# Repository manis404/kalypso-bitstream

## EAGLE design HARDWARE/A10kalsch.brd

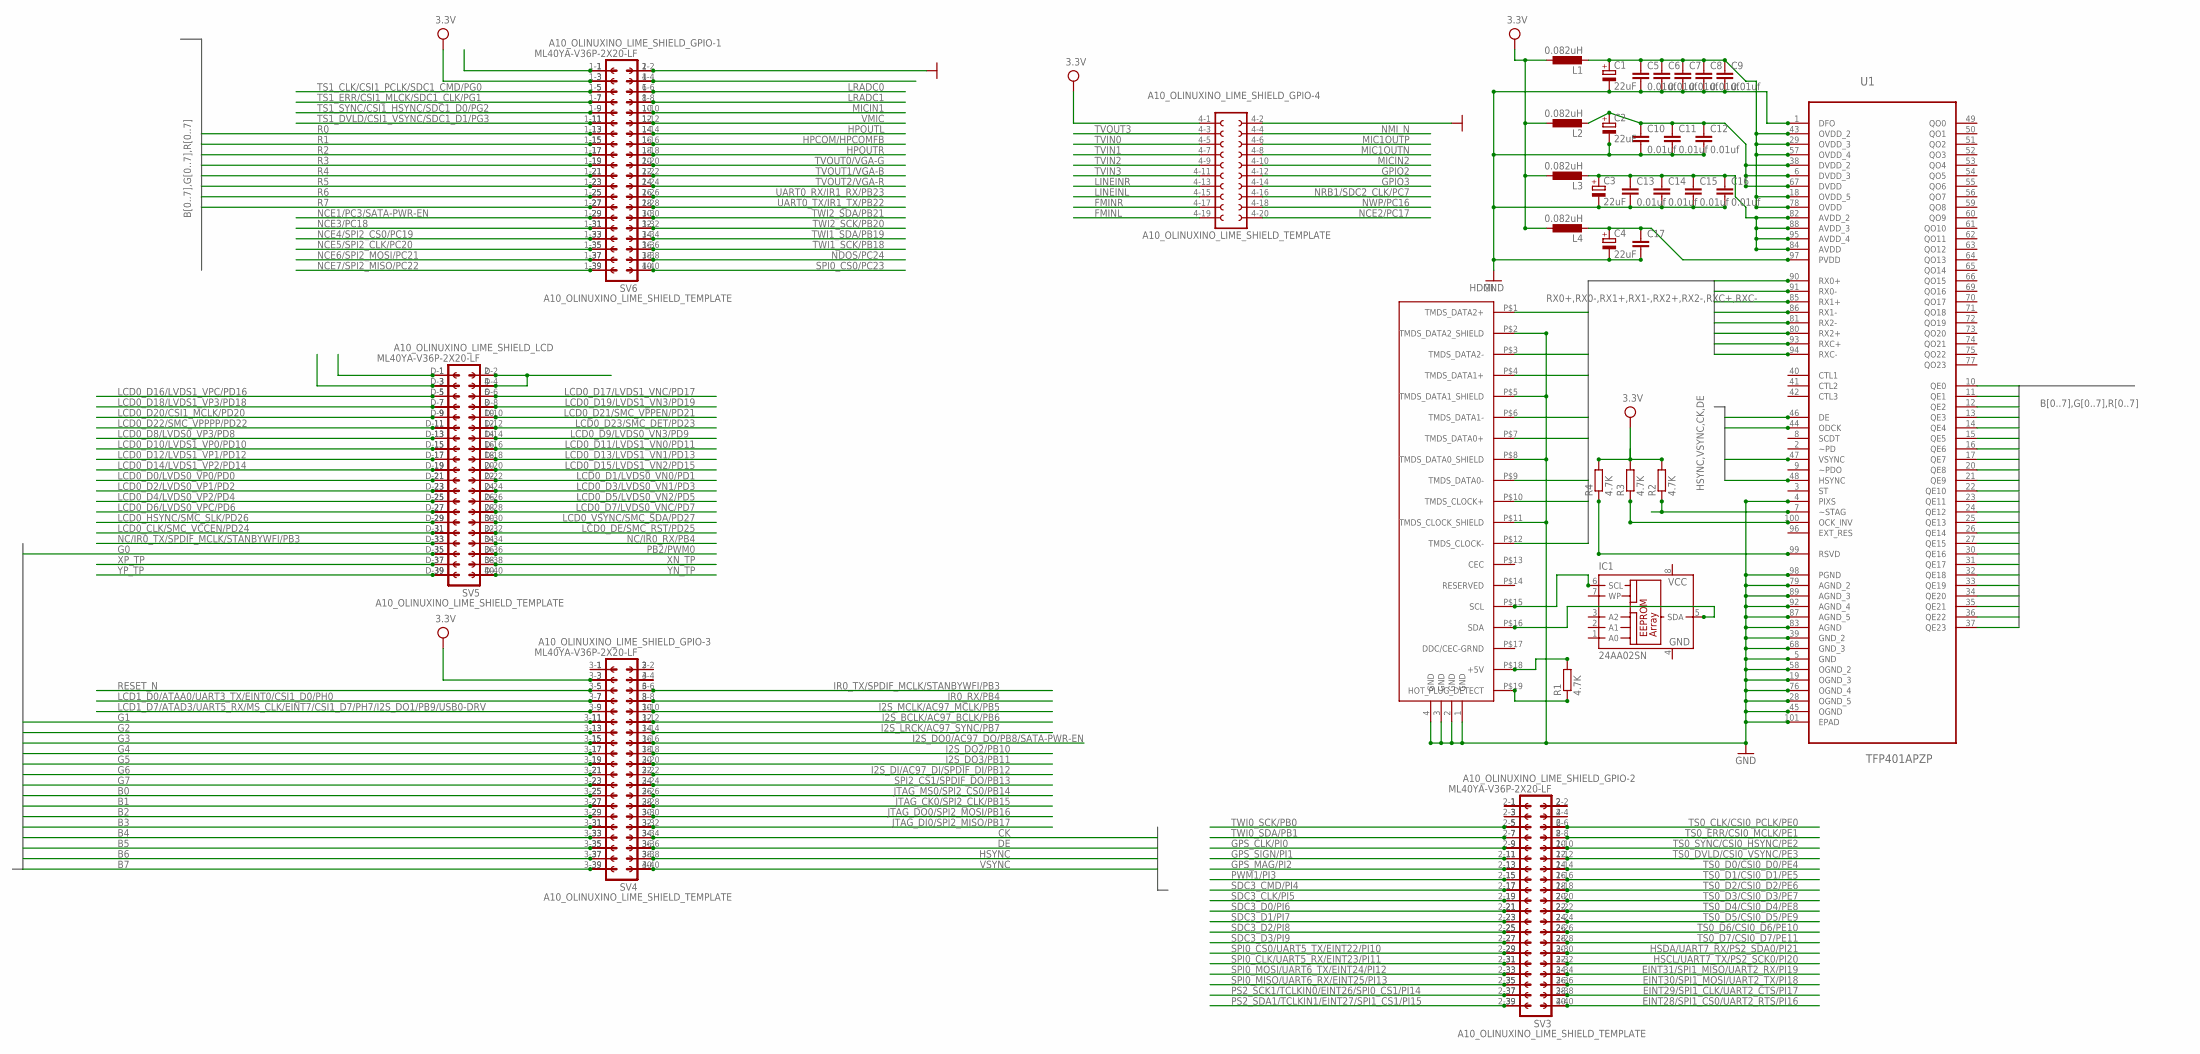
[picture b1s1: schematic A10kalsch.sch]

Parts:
A10_OLINUXINO_LIME_SHIELD: A10_OLINUXINO_LIME_SHIELD_TEMPLATE; A10_OLINUXINO_LIME_SHIELD
C1, C2, C3, C4: 22uF; CT3216
C5, C6, C7, C8, C9, C10, C11, C12, C13, C14, C15, C16: 0.01uf; C0402
C17: C-EUC0402; C0402
HDMI: HDMI; FCI-HDMI
IC1: 24AA02SN; SO-08
L1, L2, L3, L4: 0.082uH; L2012C
R1, R2, R3, R4: 4.7K; R0603
SV3, SV4, SV5, SV6: ML40YA-V36P-2X20-LF; YA-V36P-2X20-LF
U1: TFP401APZP; QFP50P1600X1600X120-101N

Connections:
B0: A10_OLINUXINO_LIME_SHIELD.3-25 (25), SV4.25, U1.10 (QE0)
B1: A10_OLINUXINO_LIME_SHIELD.3-27 (27), SV4.27, U1.11 (QE1)
B2: A10_OLINUXINO_LIME_SHIELD.3-29 (29), SV4.29, U1.12 (QE2)
B3: A10_OLINUXINO_LIME_SHIELD.3-31 (31), SV4.31, U1.13 (QE3)
B4: A10_OLINUXINO_LIME_SHIELD.3-33 (33), SV4.33, U1.14 (QE4)
B5: A10_OLINUXINO_LIME_SHIELD.3-35 (35), SV4.35, U1.15 (QE5)
B6: A10_OLINUXINO_LIME_SHIELD.3-37 (37), SV4.37, U1.16 (QE6)
B7: A10_OLINUXINO_LIME_SHIELD.3-39 (39), SV4.39, U1.17 (QE7)
CK: A10_OLINUXINO_LIME_SHIELD.3-34 (34), SV4.34, U1.44 (ODCK)
DE: A10_OLINUXINO_LIME_SHIELD.3-36 (36), SV4.36, U1.46 (DE)
EINT28/SPI1_CS0/UART2_RTS/PI16: A10_OLINUXINO_LIME_SHIELD.2-40 (40), SV3.40
EINT29/SPI1_CLK/UART2_CTS/PI17: A10_OLINUXINO_LIME_SHIELD.2-38 (38), SV3.38
EINT30/SPI1_MOSI/UART2_TX/PI18: A10_OLINUXINO_LIME_SHIELD.2-36 (36), SV3.36
EINT31/SPI1_MISO/UART2_RX/PI19: A10_OLINUXINO_LIME_SHIELD.2-34 (34), SV3.34
FMINL: A10_OLINUXINO_LIME_SHIELD.4-19 (19)
FMINR: A10_OLINUXINO_LIME_SHIELD.4-17 (17)
G0: A10_OLINUXINO_LIME_SHIELD.D-35 (35), SV5.35, U1.20 (QE8)
G1: A10_OLINUXINO_LIME_SHIELD.3-11 (11), SV4.11, U1.21 (QE9)
G2: A10_OLINUXINO_LIME_SHIELD.3-13 (13), SV4.13, U1.22 (QE10)
G3: A10_OLINUXINO_LIME_SHIELD.3-15 (15), SV4.15, U1.23 (QE11)
G4: A10_OLINUXINO_LIME_SHIELD.3-17 (17), SV4.17, U1.24 (QE12)
G5: A10_OLINUXINO_LIME_SHIELD.3-19 (19), SV4.19, U1.25 (QE13)
G6: A10_OLINUXINO_LIME_SHIELD.3-21 (21), SV4.21, U1.26 (QE14)
G7: A10_OLINUXINO_LIME_SHIELD.3-23 (23), SV4.23, U1.27 (QE15)
GND: A10_OLINUXINO_LIME_SHIELD.1-2 (2), A10_OLINUXINO_LIME_SHIELD.4-2 (2), C1.-, C2.-, C3.-, C4.-, C5.2, C6.2, C7.2, C8.2, C9.2, C10.2, C11.2, C12.2, C13.2, C14.2, C15.2, C16.2, C17.2, HDMI.1 (GND), HDMI.2 (GND), HDMI.3 (GND), HDMI.4 (GND), HDMI.P$2 (TMDS_DATA2_SHIELD), HDMI.P$5 (TMDS_DATA1_SHIELD), HDMI.P$8 (TMDS_DATA0_SHIELD), HDMI.P$11 (TMDS_CLOCK_SHIELD), IC1.4 (GND), SV6.2, U1.1 (DFO), U1.4 (PIXS), U1.5 (GND), U1.19 (OGND_3), U1.28 (OGND_5), U1.39 (GND_2), U1.45 (OGND), U1.58 (OGND_2), U1.68 (GND_3), U1.76 (OGND_4), U1.79 (AGND_2), U1.83 (AGND), U1.87 (AGND_5), U1.89 (AGND_3), U1.92 (AGND_4), U1.98 (PGND), U1.101 (EPAD)
GPIO2: A10_OLINUXINO_LIME_SHIELD.4-12 (12)
GPIO3: A10_OLINUXINO_LIME_SHIELD.4-14 (14)
GPS_CLK/PI0: A10_OLINUXINO_LIME_SHIELD.2-9 (9), SV3.9
GPS_MAG/PI2: A10_OLINUXINO_LIME_SHIELD.2-13 (13), SV3.13
GPS_SIGN/PI1: A10_OLINUXINO_LIME_SHIELD.2-11 (11), SV3.11
HPCOM/HPCOMFB: A10_OLINUXINO_LIME_SHIELD.1-16 (16), SV6.16
HPOUTL: A10_OLINUXINO_LIME_SHIELD.1-14 (14), SV6.14
HPOUTR: A10_OLINUXINO_LIME_SHIELD.1-18 (18), SV6.18
HSCL/UART7_TX/PS2_SCK0/PI20: A10_OLINUXINO_LIME_SHIELD.2-32 (32), SV3.32
HSDA/UART7_RX/PS2_SDA0/PI21: A10_OLINUXINO_LIME_SHIELD.2-30 (30), SV3.30
HSYNC: A10_OLINUXINO_LIME_SHIELD.3-38 (38), SV4.38, U1.48 (HSYNC)
I2S_BCLK/AC97_BCLK/PB6: A10_OLINUXINO_LIME_SHIELD.3-12 (12), SV4.12
I2S_DI/AC97_DI/SPDIF_DI/PB12: A10_OLINUXINO_LIME_SHIELD.3-22 (22), SV4.22
I2S_DO0/AC97_DO/PB8/SATA-PWR-EN: A10_OLINUXINO_LIME_SHIELD.3-16 (16), SV4.16
I2S_DO2/PB10: A10_OLINUXINO_LIME_SHIELD.3-18 (18), SV4.18
I2S_DO3/PB11: A10_OLINUXINO_LIME_SHIELD.3-20 (20), SV4.20
I2S_LRCK/AC97_SYNC/PB7: A10_OLINUXINO_LIME_SHIELD.3-14 (14), SV4.14
I2S_MCLK/AC97_MCLK/PB5: A10_OLINUXINO_LIME_SHIELD.3-10 (10), SV4.10
IR0_RX/PB4: A10_OLINUXINO_LIME_SHIELD.3-8 (8), SV4.8
IR0_TX/SPDIF_MCLK/STANBYWFI/PB3: A10_OLINUXINO_LIME_SHIELD.3-6 (6), SV4.6
JTAG_CK0/SPI2_CLK/PB15: A10_OLINUXINO_LIME_SHIELD.3-28 (28), SV4.28
JTAG_DI0/SPI2_MISO/PB17: A10_OLINUXINO_LIME_SHIELD.3-32 (32), SV4.32
JTAG_DO0/SPI2_MOSI/PB16: A10_OLINUXINO_LIME_SHIELD.3-30 (30), SV4.30
JTAG_MS0/SPI2_CS0/PB14: A10_OLINUXINO_LIME_SHIELD.3-26 (26), SV4.26
LCD0_CLK/SMC_VCCEN/PD24: A10_OLINUXINO_LIME_SHIELD.D-31 (31), SV5.31
LCD0_D0/LVDS0_VP0/PD0: A10_OLINUXINO_LIME_SHIELD.D-21 (21), SV5.21
LCD0_D1/LVDS0_VN0/PD1: A10_OLINUXINO_LIME_SHIELD.D-22 (22), SV5.22
LCD0_D2/LVDS0_VP1/PD2: A10_OLINUXINO_LIME_SHIELD.D-23 (23), SV5.23
LCD0_D3/LVDS0_VN1/PD3: A10_OLINUXINO_LIME_SHIELD.D-24 (24), SV5.24
LCD0_D4/LVDS0_VP2/PD4: A10_OLINUXINO_LIME_SHIELD.D-25 (25), SV5.25
LCD0_D5/LVDS0_VN2/PD5: A10_OLINUXINO_LIME_SHIELD.D-26 (26), SV5.26
LCD0_D6/LVDS0_VPC/PD6: A10_OLINUXINO_LIME_SHIELD.D-27 (27), SV5.27
LCD0_D7/LVDS0_VNC/PD7: A10_OLINUXINO_LIME_SHIELD.D-28 (28), SV5.28
LCD0_D8/LVDS0_VP3/PD8: A10_OLINUXINO_LIME_SHIELD.D-13 (13), SV5.13
LCD0_D9/LVDS0_VN3/PD9: A10_OLINUXINO_LIME_SHIELD.D-14 (14), SV5.14
LCD0_D10/LVDS1_VP0/PD10: A10_OLINUXINO_LIME_SHIELD.D-15 (15), SV5.15
LCD0_D11/LVDS1_VN0/PD11: A10_OLINUXINO_LIME_SHIELD.D-16 (16), SV5.16
LCD0_D12/LVDS1_VP1/PD12: A10_OLINUXINO_LIME_SHIELD.D-17 (17), SV5.17
LCD0_D13/LVDS1_VN1/PD13: A10_OLINUXINO_LIME_SHIELD.D-18 (18), SV5.18
LCD0_D14/LVDS1_VP2/PD14: A10_OLINUXINO_LIME_SHIELD.D-19 (19), SV5.19
LCD0_D15/LVDS1_VN2/PD15: A10_OLINUXINO_LIME_SHIELD.D-20 (20), SV5.20
LCD0_D16/LVDS1_VPC/PD16: A10_OLINUXINO_LIME_SHIELD.D-5 (5), SV5.5
LCD0_D17/LVDS1_VNC/PD17: A10_OLINUXINO_LIME_SHIELD.D-6 (6), SV5.6
LCD0_D18/LVDS1_VP3/PD18: A10_OLINUXINO_LIME_SHIELD.D-7 (7), SV5.7
LCD0_D19/LVDS1_VN3/PD19: A10_OLINUXINO_LIME_SHIELD.D-8 (8), SV5.8
LCD0_D20/CSI1_MCLK/PD20: A10_OLINUXINO_LIME_SHIELD.D-9 (9), SV5.9
LCD0_D21/SMC_VPPEN/PD21: A10_OLINUXINO_LIME_SHIELD.D-10 (10), SV5.10
LCD0_D22/SMC_VPPPP/PD22: A10_OLINUXINO_LIME_SHIELD.D-11 (11), SV5.11
LCD0_D23/SMC_DET/PD23: A10_OLINUXINO_LIME_SHIELD.D-12 (12), SV5.12
LCD0_DE/SMC_RST/PD25: A10_OLINUXINO_LIME_SHIELD.D-32 (32), SV5.32
LCD0_HSYNC/SMC_SLK/PD26: A10_OLINUXINO_LIME_SHIELD.D-29 (29), SV5.29
LCD0_VSYNC/SMC_SDA/PD27: A10_OLINUXINO_LIME_SHIELD.D-30 (30), SV5.30
LCD1_D0/ATAA0/UART3_TX/EINT0/CSI1_D0/PH0: A10_OLINUXINO_LIME_SHIELD.3-7 (7), SV4.7
LCD1_D7/ATAD3/UART5_RX/MS_CLK/EINT7/CSI1_D7/PH7/I2S_DO1/PB9/USB0-DRV: A10_OLINUXINO_LIME_SHIELD.3-9 (9), SV4.9
LINEINL: A10_OLINUXINO_LIME_SHIELD.4-15 (15)
LINEINR: A10_OLINUXINO_LIME_SHIELD.4-13 (13)
LRADC0: A10_OLINUXINO_LIME_SHIELD.1-6 (6), SV6.6
LRADC1: A10_OLINUXINO_LIME_SHIELD.1-8 (8), SV6.8
MIC1OUTN: A10_OLINUXINO_LIME_SHIELD.4-8 (8)
MIC1OUTP: A10_OLINUXINO_LIME_SHIELD.4-6 (6)
MICIN1: A10_OLINUXINO_LIME_SHIELD.1-10 (10), SV6.10
MICIN2: A10_OLINUXINO_LIME_SHIELD.4-10 (10)
unnamed: A10_OLINUXINO_LIME_SHIELD.1-4 (4), SV6.4
unnamed: R2.1, U1.7 (~STAG)
unnamed: R3.1, U1.100 (OCK_INV)
unnamed: R4.1, U1.99 (RSVD)
unnamed: A10_OLINUXINO_LIME_SHIELD.D-3 (3), SV5.3
unnamed: C2.+, C10.1, C11.1, C12.1, L2.2, U1.6 (DVDD_3), U1.38 (DVDD_2), U1.67 (DVDD)
unnamed: C4.+, C17.1, L4.2, U1.97 (PVDD)
unnamed: C3.+, C13.1, C14.1, C15.1, C16.1, L3.2, U1.82 (AVDD_2), U1.84 (AVDD), U1.88 (AVDD_3), U1.95 (AVDD_4)
unnamed: C1.+, C5.1, C6.1, C7.1, C8.1, C9.1, L1.2, U1.18 (OVDD_5), U1.29 (OVDD_3), U1.43 (OVDD_2), U1.57 (OVDD_4), U1.78 (OVDD)
unnamed: A10_OLINUXINO_LIME_SHIELD.D-1 (1), SV5.1
unnamed: A10_OLINUXINO_LIME_SHIELD.D-2 (2), A10_OLINUXINO_LIME_SHIELD.D-4 (4), SV5.2, SV5.4
unnamed: A10_OLINUXINO_LIME_SHIELD.1-1 (1), SV6.1
unnamed: HDMI.P$18 (+5V), R1.2
unnamed: HDMI.P$19 (HOT_PLUG_DETECT), R1.1
unnamed: A10_OLINUXINO_LIME_SHIELD.2-1 (1), SV3.1
unnamed: A10_OLINUXINO_LIME_SHIELD.2-2 (2), SV3.2
unnamed: A10_OLINUXINO_LIME_SHIELD.2-3 (3), SV3.3
unnamed: A10_OLINUXINO_LIME_SHIELD.2-4 (4), SV3.4
unnamed: A10_OLINUXINO_LIME_SHIELD.3-1 (1), SV4.1
unnamed: A10_OLINUXINO_LIME_SHIELD.3-2 (2), SV4.2
unnamed: A10_OLINUXINO_LIME_SHIELD.3-4 (4), SV4.4
unnamed: HDMI.P$15 (SCL), IC1.6 (SCL)
unnamed: HDMI.P$16 (SDA), IC1.5 (SDA)
NC/IR0_RX/PB4: A10_OLINUXINO_LIME_SHIELD.D-34 (34), SV5.34
NC/IR0_TX/SPDIF_MCLK/STANBYWFI/PB3: A10_OLINUXINO_LIME_SHIELD.D-33 (33), SV5.33
NCE1/PC3/SATA-PWR-EN: A10_OLINUXINO_LIME_SHIELD.1-29 (29), SV6.29
NCE2/PC17: A10_OLINUXINO_LIME_SHIELD.4-20 (20)
NCE3/PC18: A10_OLINUXINO_LIME_SHIELD.1-31 (31), SV6.31
NCE4/SPI2_CS0/PC19: A10_OLINUXINO_LIME_SHIELD.1-33 (33), SV6.33
NCE5/SPI2_CLK/PC20: A10_OLINUXINO_LIME_SHIELD.1-35 (35), SV6.35
NCE6/SPI2_MOSI/PC21: A10_OLINUXINO_LIME_SHIELD.1-37 (37), SV6.37
NCE7/SPI2_MISO/PC22: A10_OLINUXINO_LIME_SHIELD.1-39 (39), SV6.39
NDQS/PC24: A10_OLINUXINO_LIME_SHIELD.1-38 (38), SV6.38
NMI_N: A10_OLINUXINO_LIME_SHIELD.4-4 (4)
NRB1/SDC2_CLK/PC7: A10_OLINUXINO_LIME_SHIELD.4-16 (16)
NWP/PC16: A10_OLINUXINO_LIME_SHIELD.4-18 (18)
PB2/PWM0: A10_OLINUXINO_LIME_SHIELD.D-36 (36), SV5.36
PS2_SCK1/TCLKIN0/EINT26/SPI0_CS1/PI14: A10_OLINUXINO_LIME_SHIELD.2-37 (37), SV3.37
PS2_SDA1/TCLKIN1/EINT27/SPI1_CS1/PI15: A10_OLINUXINO_LIME_SHIELD.2-39 (39), SV3.39
PWM1/PI3: A10_OLINUXINO_LIME_SHIELD.2-15 (15), SV3.15
R0: A10_OLINUXINO_LIME_SHIELD.1-13 (13), SV6.13, U1.30 (QE16)
R1: A10_OLINUXINO_LIME_SHIELD.1-15 (15), SV6.15, U1.31 (QE17)
R2: A10_OLINUXINO_LIME_SHIELD.1-17 (17), SV6.17, U1.32 (QE18)
R3: A10_OLINUXINO_LIME_SHIELD.1-19 (19), SV6.19, U1.33 (QE19)
R4: A10_OLINUXINO_LIME_SHIELD.1-21 (21), SV6.21, U1.34 (QE20)
R5: A10_OLINUXINO_LIME_SHIELD.1-23 (23), SV6.23, U1.35 (QE21)
R6: A10_OLINUXINO_LIME_SHIELD.1-25 (25), SV6.25, U1.36 (QE22)
R7: A10_OLINUXINO_LIME_SHIELD.1-27 (27), SV6.27, U1.37 (QE23)
RESET_N: A10_OLINUXINO_LIME_SHIELD.3-5 (5), SV4.5
RX0_N: HDMI.P$9 (TMDS_DATA0-), U1.91 (RX0-)
RX0_P: HDMI.P$7 (TMDS_DATA0+), U1.90 (RX0+)
RX1_N: HDMI.P$6 (TMDS_DATA1-), U1.86 (RX1-)
RX1_P: HDMI.P$4 (TMDS_DATA1+), U1.85 (RX1+)
RX2_N: HDMI.P$3 (TMDS_DATA2-), U1.81 (RX2-)
RX2_P: HDMI.P$1 (TMDS_DATA2+), U1.80 (RX2+)
RXC_N: HDMI.P$12 (TMDS_CLOCK-), U1.94 (RXC-)
RXC_P: HDMI.P$10 (TMDS_CLOCK+), U1.93 (RXC+)
SDC3_CLK/PI5: A10_OLINUXINO_LIME_SHIELD.2-19 (19), SV3.19
SDC3_CMD/PI4: A10_OLINUXINO_LIME_SHIELD.2-17 (17), SV3.17
SDC3_D0/PI6: A10_OLINUXINO_LIME_SHIELD.2-21 (21), SV3.21
SDC3_D1/PI7: A10_OLINUXINO_LIME_SHIELD.2-23 (23), SV3.23
SDC3_D2/PI8: A10_OLINUXINO_LIME_SHIELD.2-25 (25), SV3.25
SDC3_D3/PI9: A10_OLINUXINO_LIME_SHIELD.2-27 (27), SV3.27
SPI0_CLK/UART5_RX/EINT23/PI11: A10_OLINUXINO_LIME_SHIELD.2-31 (31), SV3.31
SPI0_CS0/PC23: A10_OLINUXINO_LIME_SHIELD.1-40 (40), SV6.40
SPI0_CS0/UART5_TX/EINT22/PI10: A10_OLINUXINO_LIME_SHIELD.2-29 (29), SV3.29
SPI0_MISO/UART6_RX/EINT25/PI13: A10_OLINUXINO_LIME_SHIELD.2-35 (35), SV3.35
SPI0_MOSI/UART6_TX/EINT24/PI12: A10_OLINUXINO_LIME_SHIELD.2-33 (33), SV3.33
SPI2_CS1/SPDIF_DO/PB13: A10_OLINUXINO_LIME_SHIELD.3-24 (24), SV4.24
TS0_CLK/CSI0_PCLK/PE0: A10_OLINUXINO_LIME_SHIELD.2-6 (6), SV3.6
TS0_D0/CSI0_D0/PE4: A10_OLINUXINO_LIME_SHIELD.2-14 (14), SV3.14
TS0_D1/CSI0_D1/PE5: A10_OLINUXINO_LIME_SHIELD.2-16 (16), SV3.16
TS0_D2/CSI0_D2/PE6: A10_OLINUXINO_LIME_SHIELD.2-18 (18), SV3.18
TS0_D3/CSI0_D3/PE7: A10_OLINUXINO_LIME_SHIELD.2-20 (20), SV3.20
TS0_D4/CSI0_D4/PE8: A10_OLINUXINO_LIME_SHIELD.2-22 (22), SV3.22
TS0_D5/CSI0_D5/PE9: A10_OLINUXINO_LIME_SHIELD.2-24 (24), SV3.24
TS0_D6/CSI0_D6/PE10: A10_OLINUXINO_LIME_SHIELD.2-26 (26), SV3.26
TS0_D7/CSI0_D7/PE11: A10_OLINUXINO_LIME_SHIELD.2-28 (28), SV3.28
TS0_DVLD/CSI0_VSYNC/PE3: A10_OLINUXINO_LIME_SHIELD.2-12 (12), SV3.12
TS0_ERR/CSI0_MCLK/PE1: A10_OLINUXINO_LIME_SHIELD.2-8 (8), SV3.8
TS0_SYNC/CSI0_HSYNC/PE2: A10_OLINUXINO_LIME_SHIELD.2-10 (10), SV3.10
TS1_CLK/CSI1_PCLK/SDC1_CMD/PG0: A10_OLINUXINO_LIME_SHIELD.1-5 (5), SV6.5
TS1_DVLD/CSI1_VSYNC/SDC1_D1/PG3: A10_OLINUXINO_LIME_SHIELD.1-11 (11), SV6.11
TS1_ERR/CSI1_MLCK/SDC1_CLK/PG1: A10_OLINUXINO_LIME_SHIELD.1-7 (7), SV6.7
TS1_SYNC/CSI1_HSYNC/SDC1_D0/PG2: A10_OLINUXINO_LIME_SHIELD.1-9 (9), SV6.9
TVIN0: A10_OLINUXINO_LIME_SHIELD.4-5 (5)
TVIN1: A10_OLINUXINO_LIME_SHIELD.4-7 (7)
TVIN2: A10_OLINUXINO_LIME_SHIELD.4-9 (9)
TVIN3: A10_OLINUXINO_LIME_SHIELD.4-11 (11)
TVOUT0/VGA-G: A10_OLINUXINO_LIME_SHIELD.1-20 (20), SV6.20
TVOUT1/VGA-B: A10_OLINUXINO_LIME_SHIELD.1-22 (22), SV6.22
TVOUT2/VGA-R: A10_OLINUXINO_LIME_SHIELD.1-24 (24), SV6.24
TVOUT3: A10_OLINUXINO_LIME_SHIELD.4-3 (3)
TWI0_SCK/PB0: A10_OLINUXINO_LIME_SHIELD.2-5 (5), SV3.5
TWI0_SDA/PB1: A10_OLINUXINO_LIME_SHIELD.2-7 (7), SV3.7
TWI1_SCK/PB18: A10_OLINUXINO_LIME_SHIELD.1-36 (36), SV6.36
TWI1_SDA/PB19: A10_OLINUXINO_LIME_SHIELD.1-34 (34), SV6.34
TWI2_SCK/PB20: A10_OLINUXINO_LIME_SHIELD.1-32 (32), SV6.32
TWI2_SDA/PB21: A10_OLINUXINO_LIME_SHIELD.1-30 (30), SV6.30
UART0_RX/IR1_RX/PB23: A10_OLINUXINO_LIME_SHIELD.1-26 (26), SV6.26
UART0_TX/IR1_TX/PB22: A10_OLINUXINO_LIME_SHIELD.1-28 (28), SV6.28
VCC: A10_OLINUXINO_LIME_SHIELD.1-3 (3), A10_OLINUXINO_LIME_SHIELD.3-3 (3), A10_OLINUXINO_LIME_SHIELD.4-1 (1), IC1.8 (VCC), L1.1, L2.1, L3.1, L4.1, R2.2, R3.2, R4.2, SV4.3, SV6.3
VMIC: A10_OLINUXINO_LIME_SHIELD.1-12 (12), SV6.12
VSYNC: A10_OLINUXINO_LIME_SHIELD.3-40 (40), SV4.40, U1.47 (VSYNC)
XN_TP: A10_OLINUXINO_LIME_SHIELD.D-38 (38), SV5.38
XP_TP: A10_OLINUXINO_LIME_SHIELD.D-37 (37), SV5.37
YN_TP: A10_OLINUXINO_LIME_SHIELD.D-40 (40), SV5.40
YP_TP: A10_OLINUXINO_LIME_SHIELD.D-39 (39), SV5.39

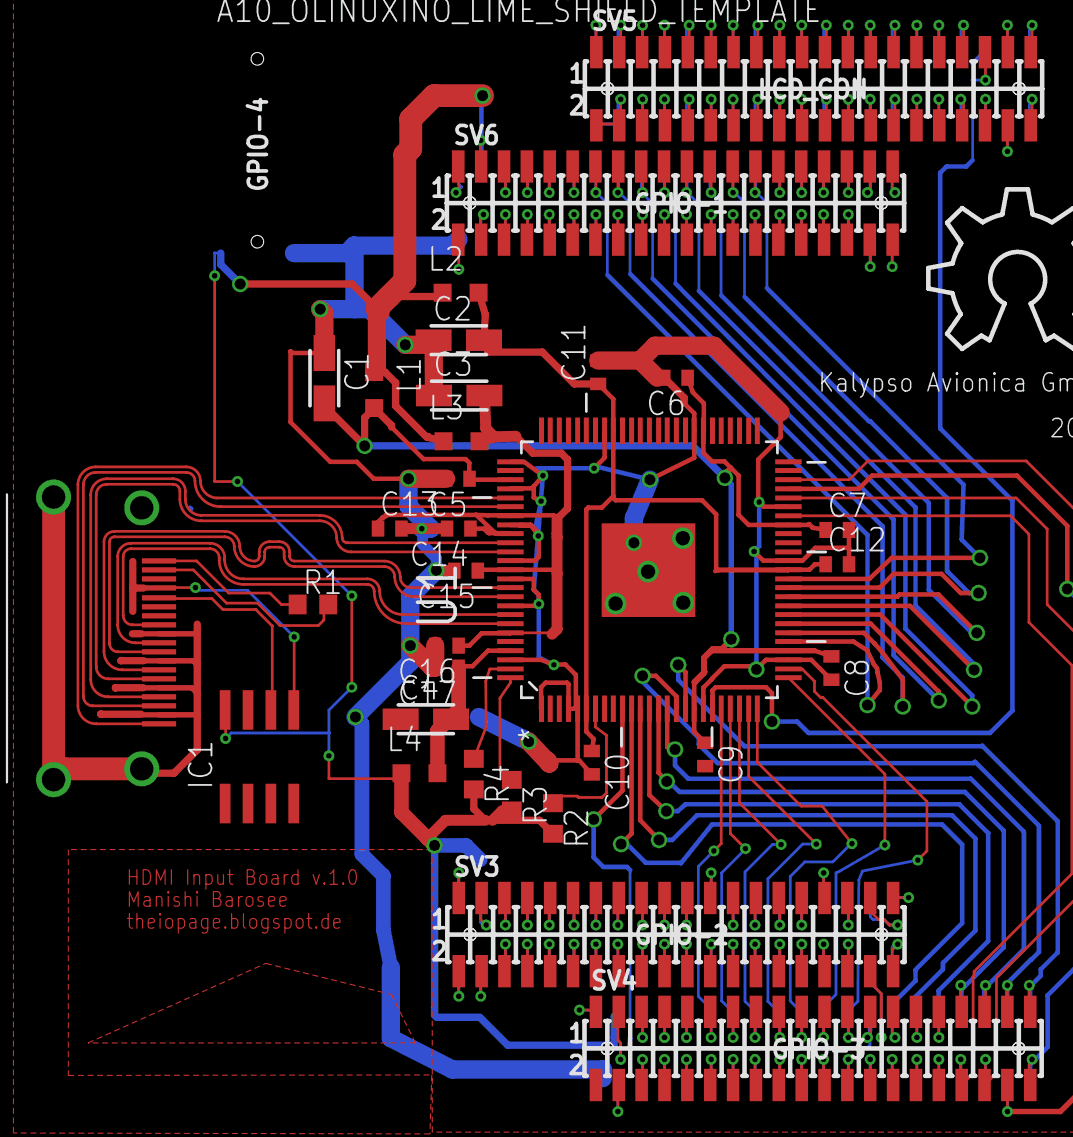
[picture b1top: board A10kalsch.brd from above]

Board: 2 copper layers, 34 parts (0 on the bottom side), 177 nets.

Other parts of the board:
U$2: OSHW_10X350_NOTEXT

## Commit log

2014-03-20 Add README.md
2014-03-20 lic init
2014-03-20 cap pcb 1
